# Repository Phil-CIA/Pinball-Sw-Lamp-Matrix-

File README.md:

# Pinball Switch + Lamp Matrix Board

8x4 lamp matrix driver and 8x4 switch matrix scanner board for a pinball machine.

## Architecture (current)
- **Lamp rows (8):** high-side smart switches (2× `VNQ7E100AJTR`, 4ch each)
- **Lamp columns (4):** low-side MOSFET sinks
- **Switch columns (4):** `LMV393` comparators (5V powered, OD outputs pulled up to 3.3V)
- **Output expansion:** 2× `74HC595` @ 3.3V for deterministic row/column bit patterns

## Repo layout
- `hardware/` – KiCad project files and production exports
- `firmware/` – PlatformIO / ESP-IDF bring-up firmware
- `docs/` – design notes, project status, review notes, and bring-up plans
- `BOM/` – key part numbers and alternates

## Project references
- `docs/PROJECT_STATUS.md` – current state, locked assumptions, and active priorities
- `docs/NEXT_ITERATION.md` – parking lot for ideas, risks, and restart notes
- `docs/SCHEMATIC_REVIEW.md` – design review and cleanup notes captured during the pre-order review
- `docs/BRINGUP_CHECKLIST.md` – first-board arrival, assembly, and power-up checklist
- `docs/PINMAP.md` – signal naming, connector grouping, and board-mating draft map
- `docs/PCB_REVIEW_CHECKLIST.md` – pre-order hardware checklist
- `docs/GITHUB_REPO_SETUP.md` – suggested GitHub repo metadata and settings
- `BOM/key_parts.md` – important component choices
- `CONTRIBUTING.md` – repo workflow and update expectations
- `SECURITY.md` – reporting guidance for risky or security-related issues
- `CHANGELOG.md` – notable repo changes over time

## Status
Rev 1 hardware was ordered on **2026-04-09**.

- **Hardware:** schematic, PCB snapshots, Gerbers, drill files, BOM, and production ZIP are checked in under `hardware/`
- **Order state:** PCB + stencil ordered, with parts ordered separately
- **Current phase:** wait for hardware and prepare bench bring-up
- **Firmware:** verified ESP32-C6 ESP-IDF bring-up scaffold is present under `firmware/`

## Next Steps
- keep the ordered Rev 1 package and notes as the reference point
- assemble and inspect the first boards when they arrive
- short-check `18V`, `5V`, and `3.3V` before full power-up
- validate ESP32, shift-register outputs, and switch-column reads on bench hardware
- run one-row / one-column lamp tests, then a full matrix scan
- capture any Rev 2 findings after first hardware validation

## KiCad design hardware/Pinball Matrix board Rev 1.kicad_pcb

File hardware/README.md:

# Hardware Notes

This folder contains the KiCad project files and production exports for the pinball switch + lamp matrix board.

## Current state
- `Pinball Matrix board Rev 1.kicad_sch` is the checked-in schematic source for Rev 1.
- `hardware/` also contains routed PCB snapshots, Gerbers, drill files, a BOM CSV, and the zipped production package used for ordering.
- Rev 1 PCB + stencil were ordered on `2026-04-09`; treat the ordered files as the frozen reference until hardware bring-up starts.

## Recommended use
1. Use `../docs/SCHEMATIC_REVIEW.md` for design review context and accepted tradeoffs.
2. Use `../docs/BRINGUP_CHECKLIST.md` when the first boards arrive.
3. Record any assembly or bench findings back into `../docs/NEXT_ITERATION.md` and `../docs/PROJECT_STATUS.md`.

## Caution
- More than one PCB snapshot exists in this folder (`pre route`, `routed`, `routed power`).
- If a post-order edit is made, clearly note whether it belongs to the frozen Rev 1 archive or to future Rev 2 work.

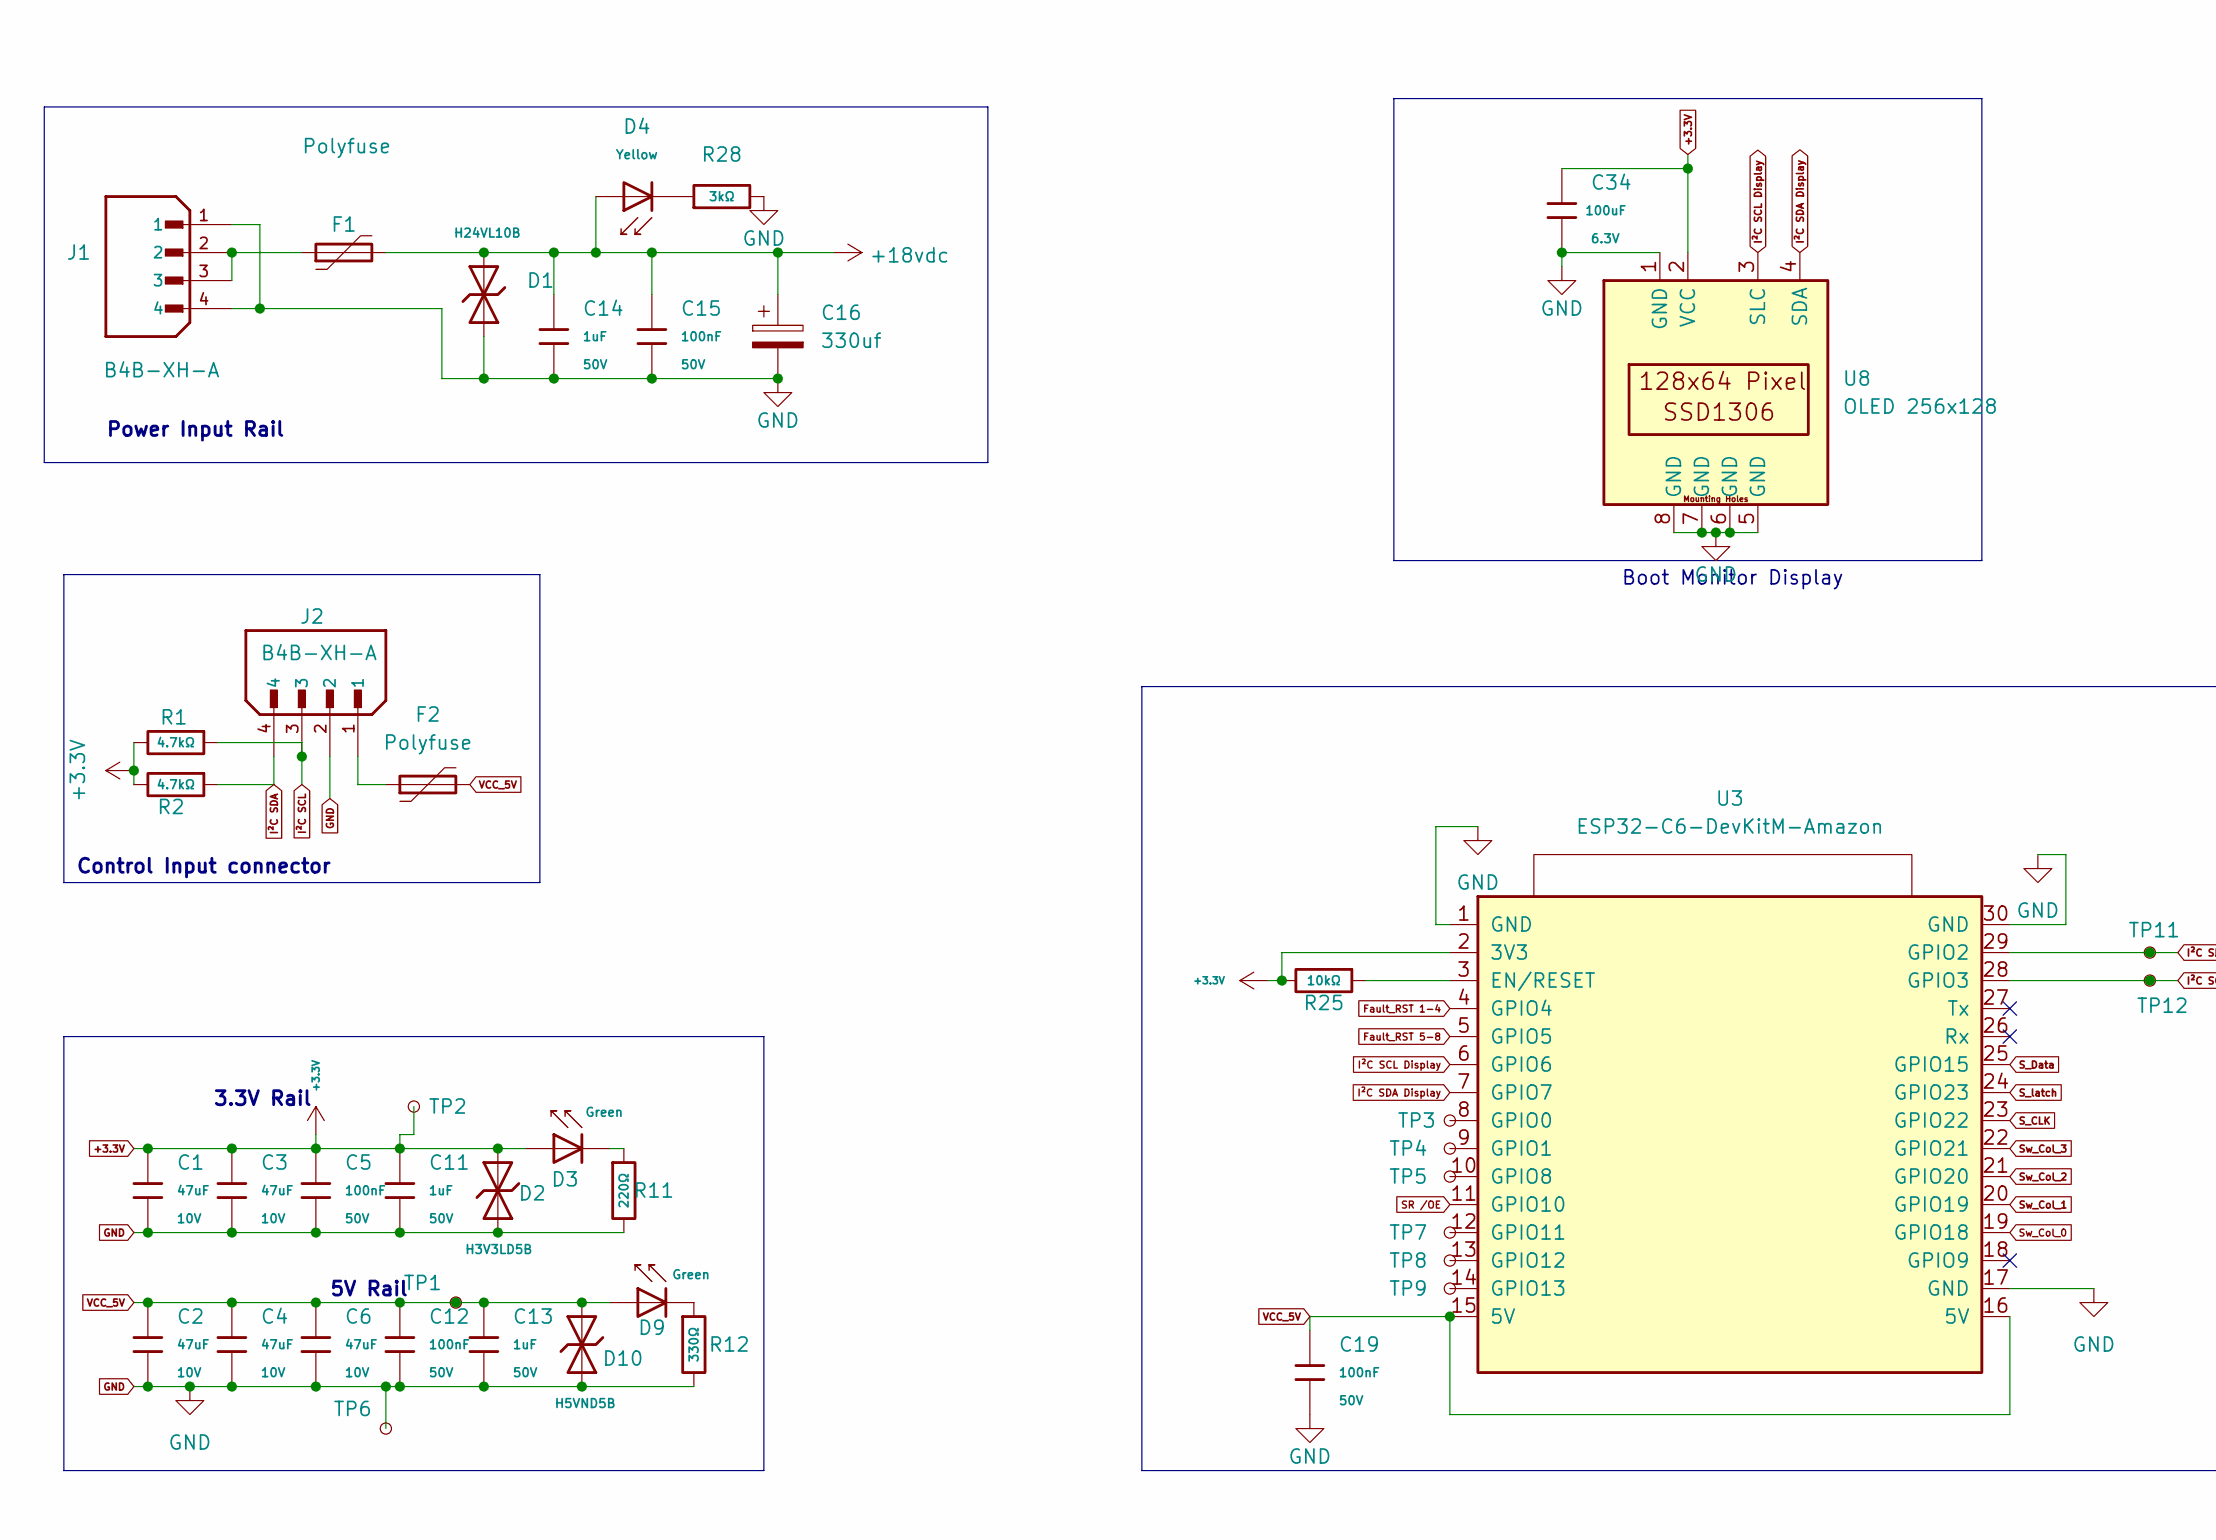
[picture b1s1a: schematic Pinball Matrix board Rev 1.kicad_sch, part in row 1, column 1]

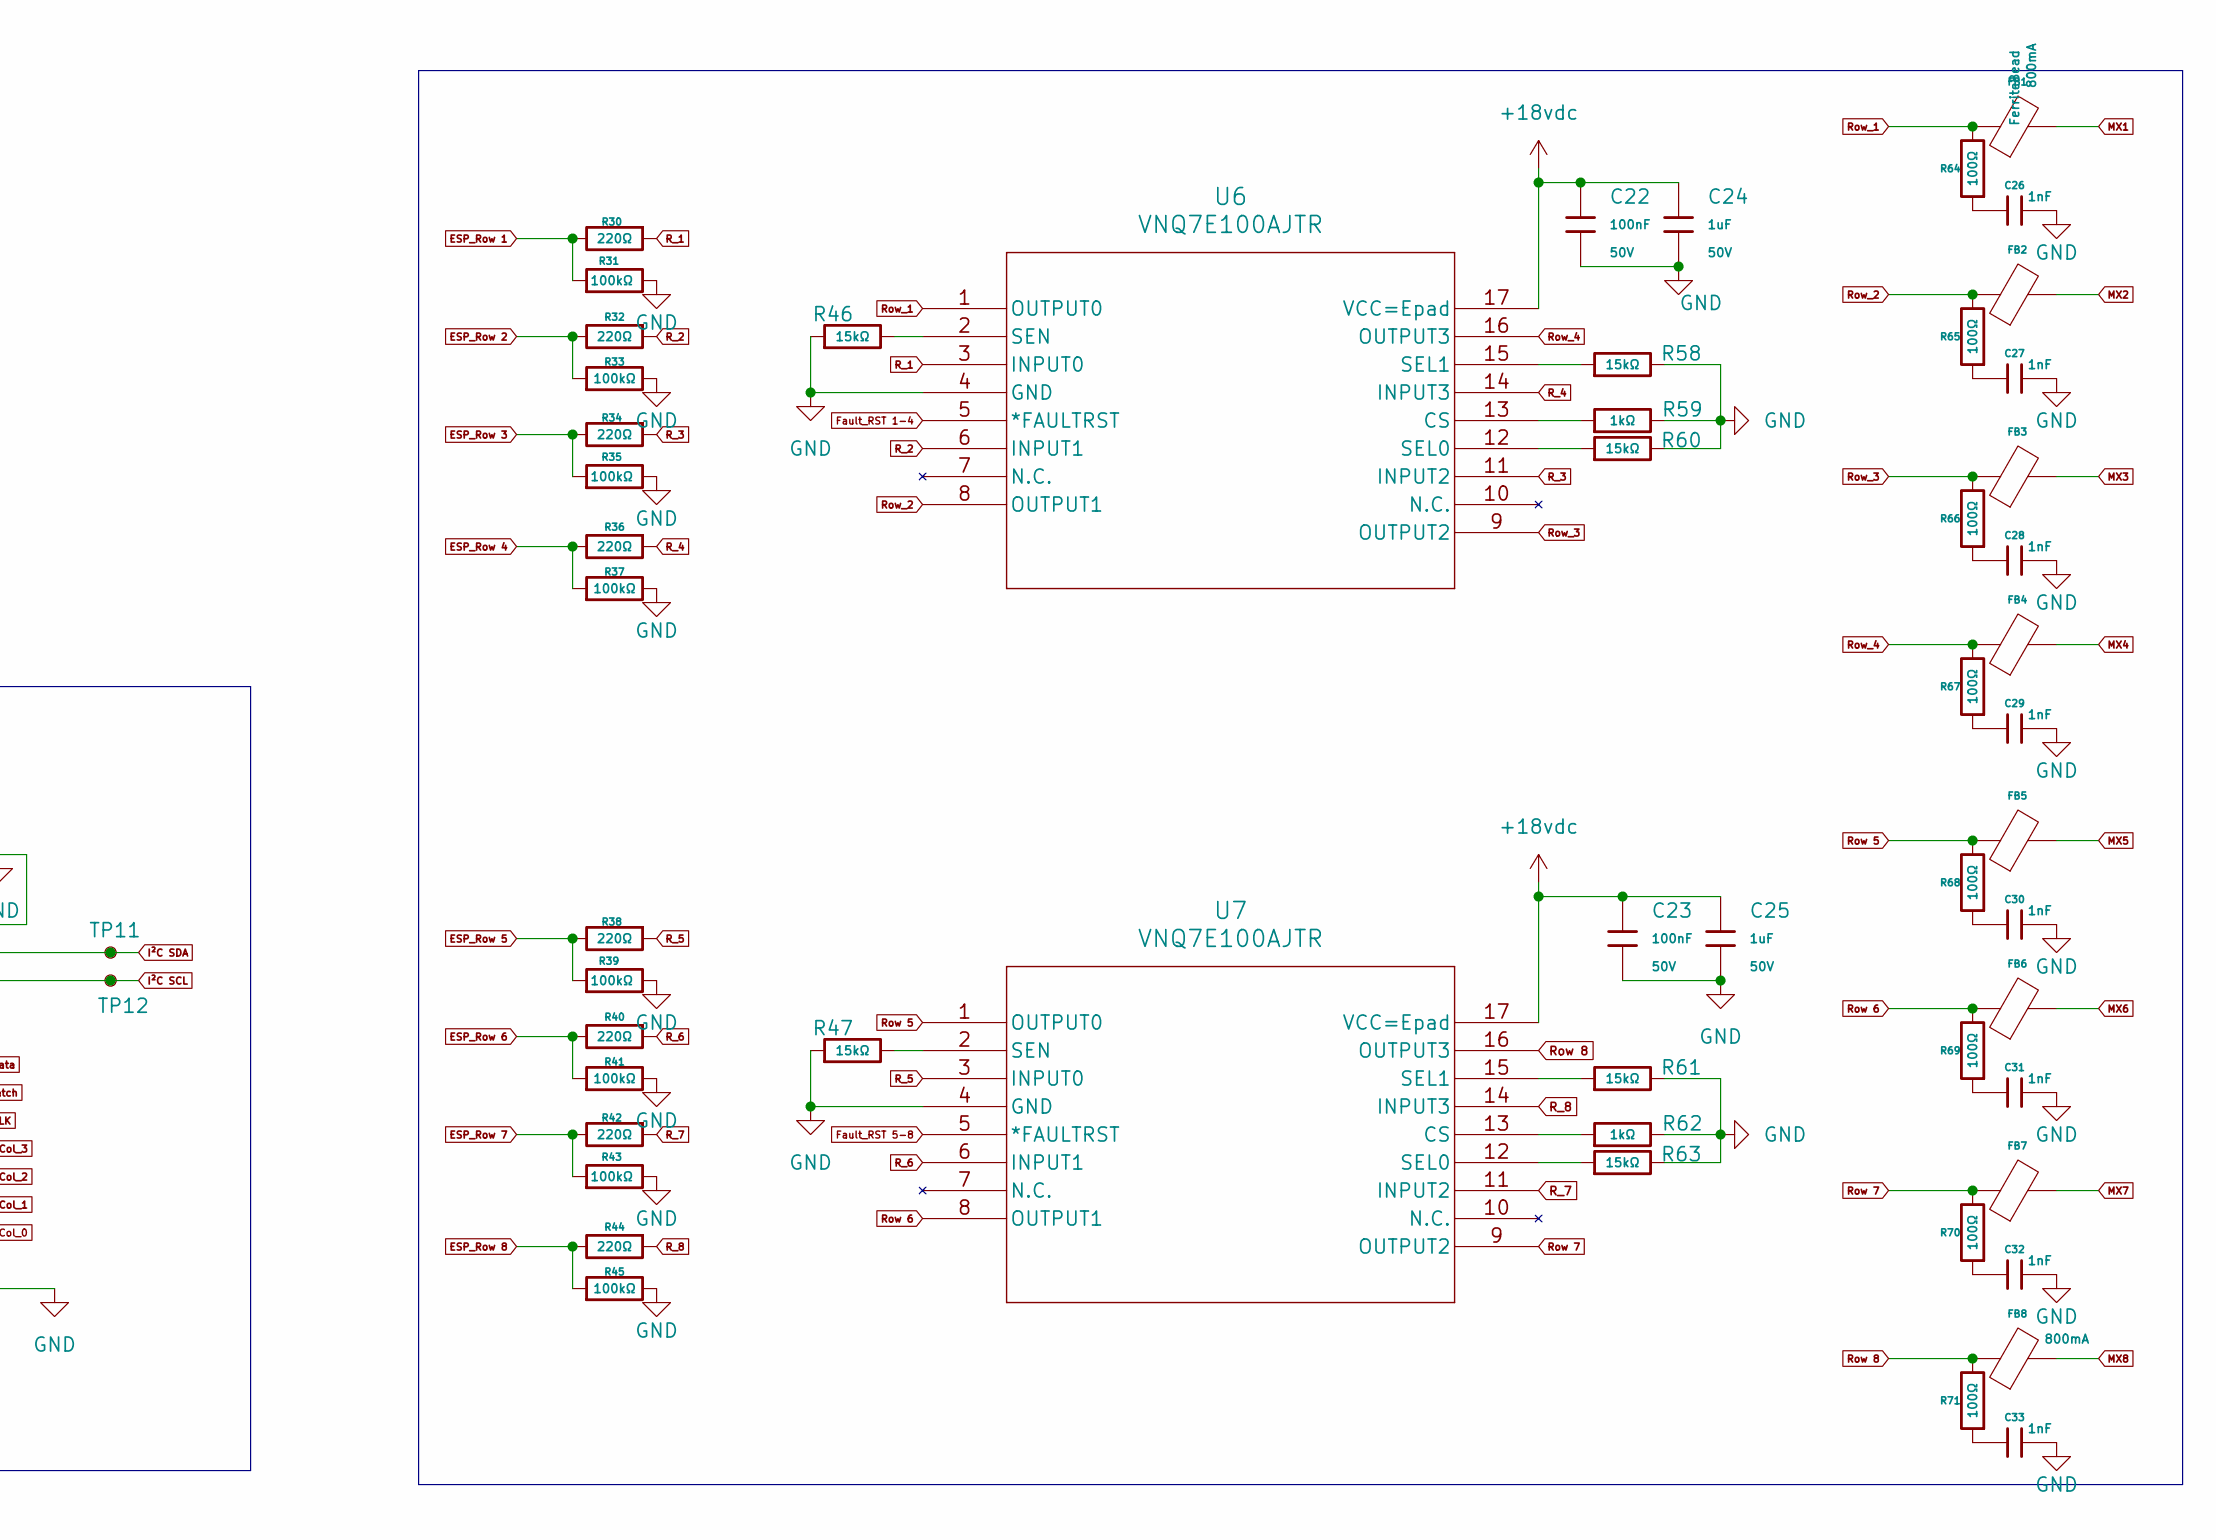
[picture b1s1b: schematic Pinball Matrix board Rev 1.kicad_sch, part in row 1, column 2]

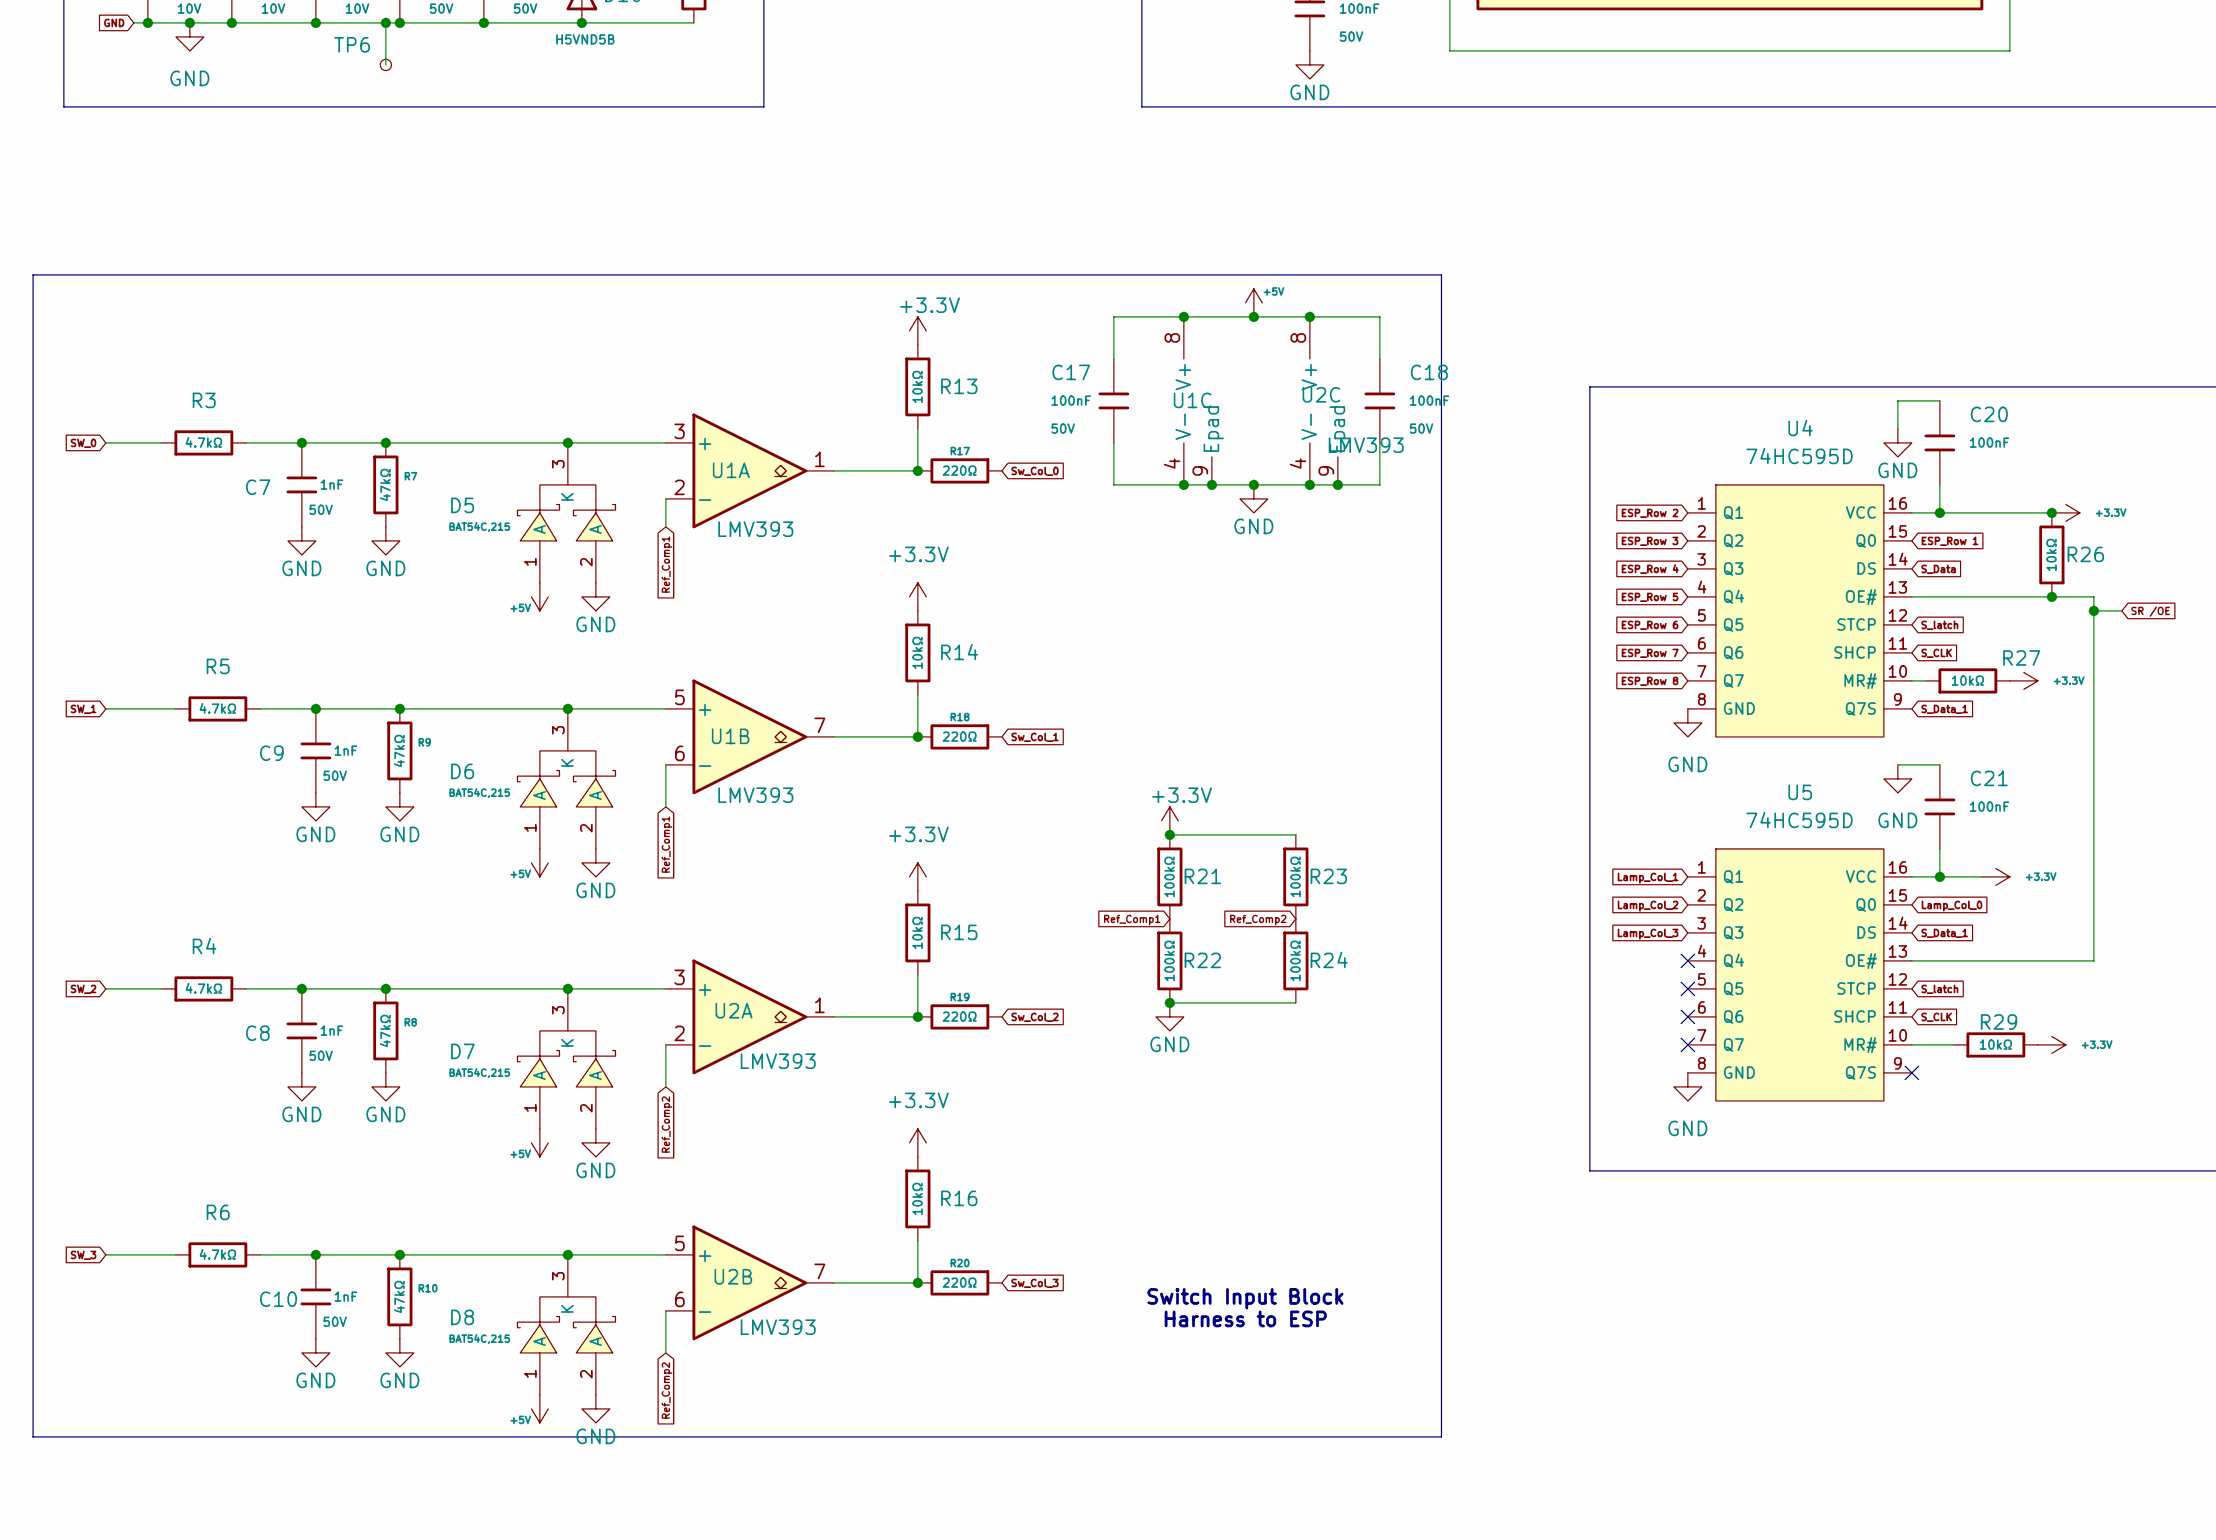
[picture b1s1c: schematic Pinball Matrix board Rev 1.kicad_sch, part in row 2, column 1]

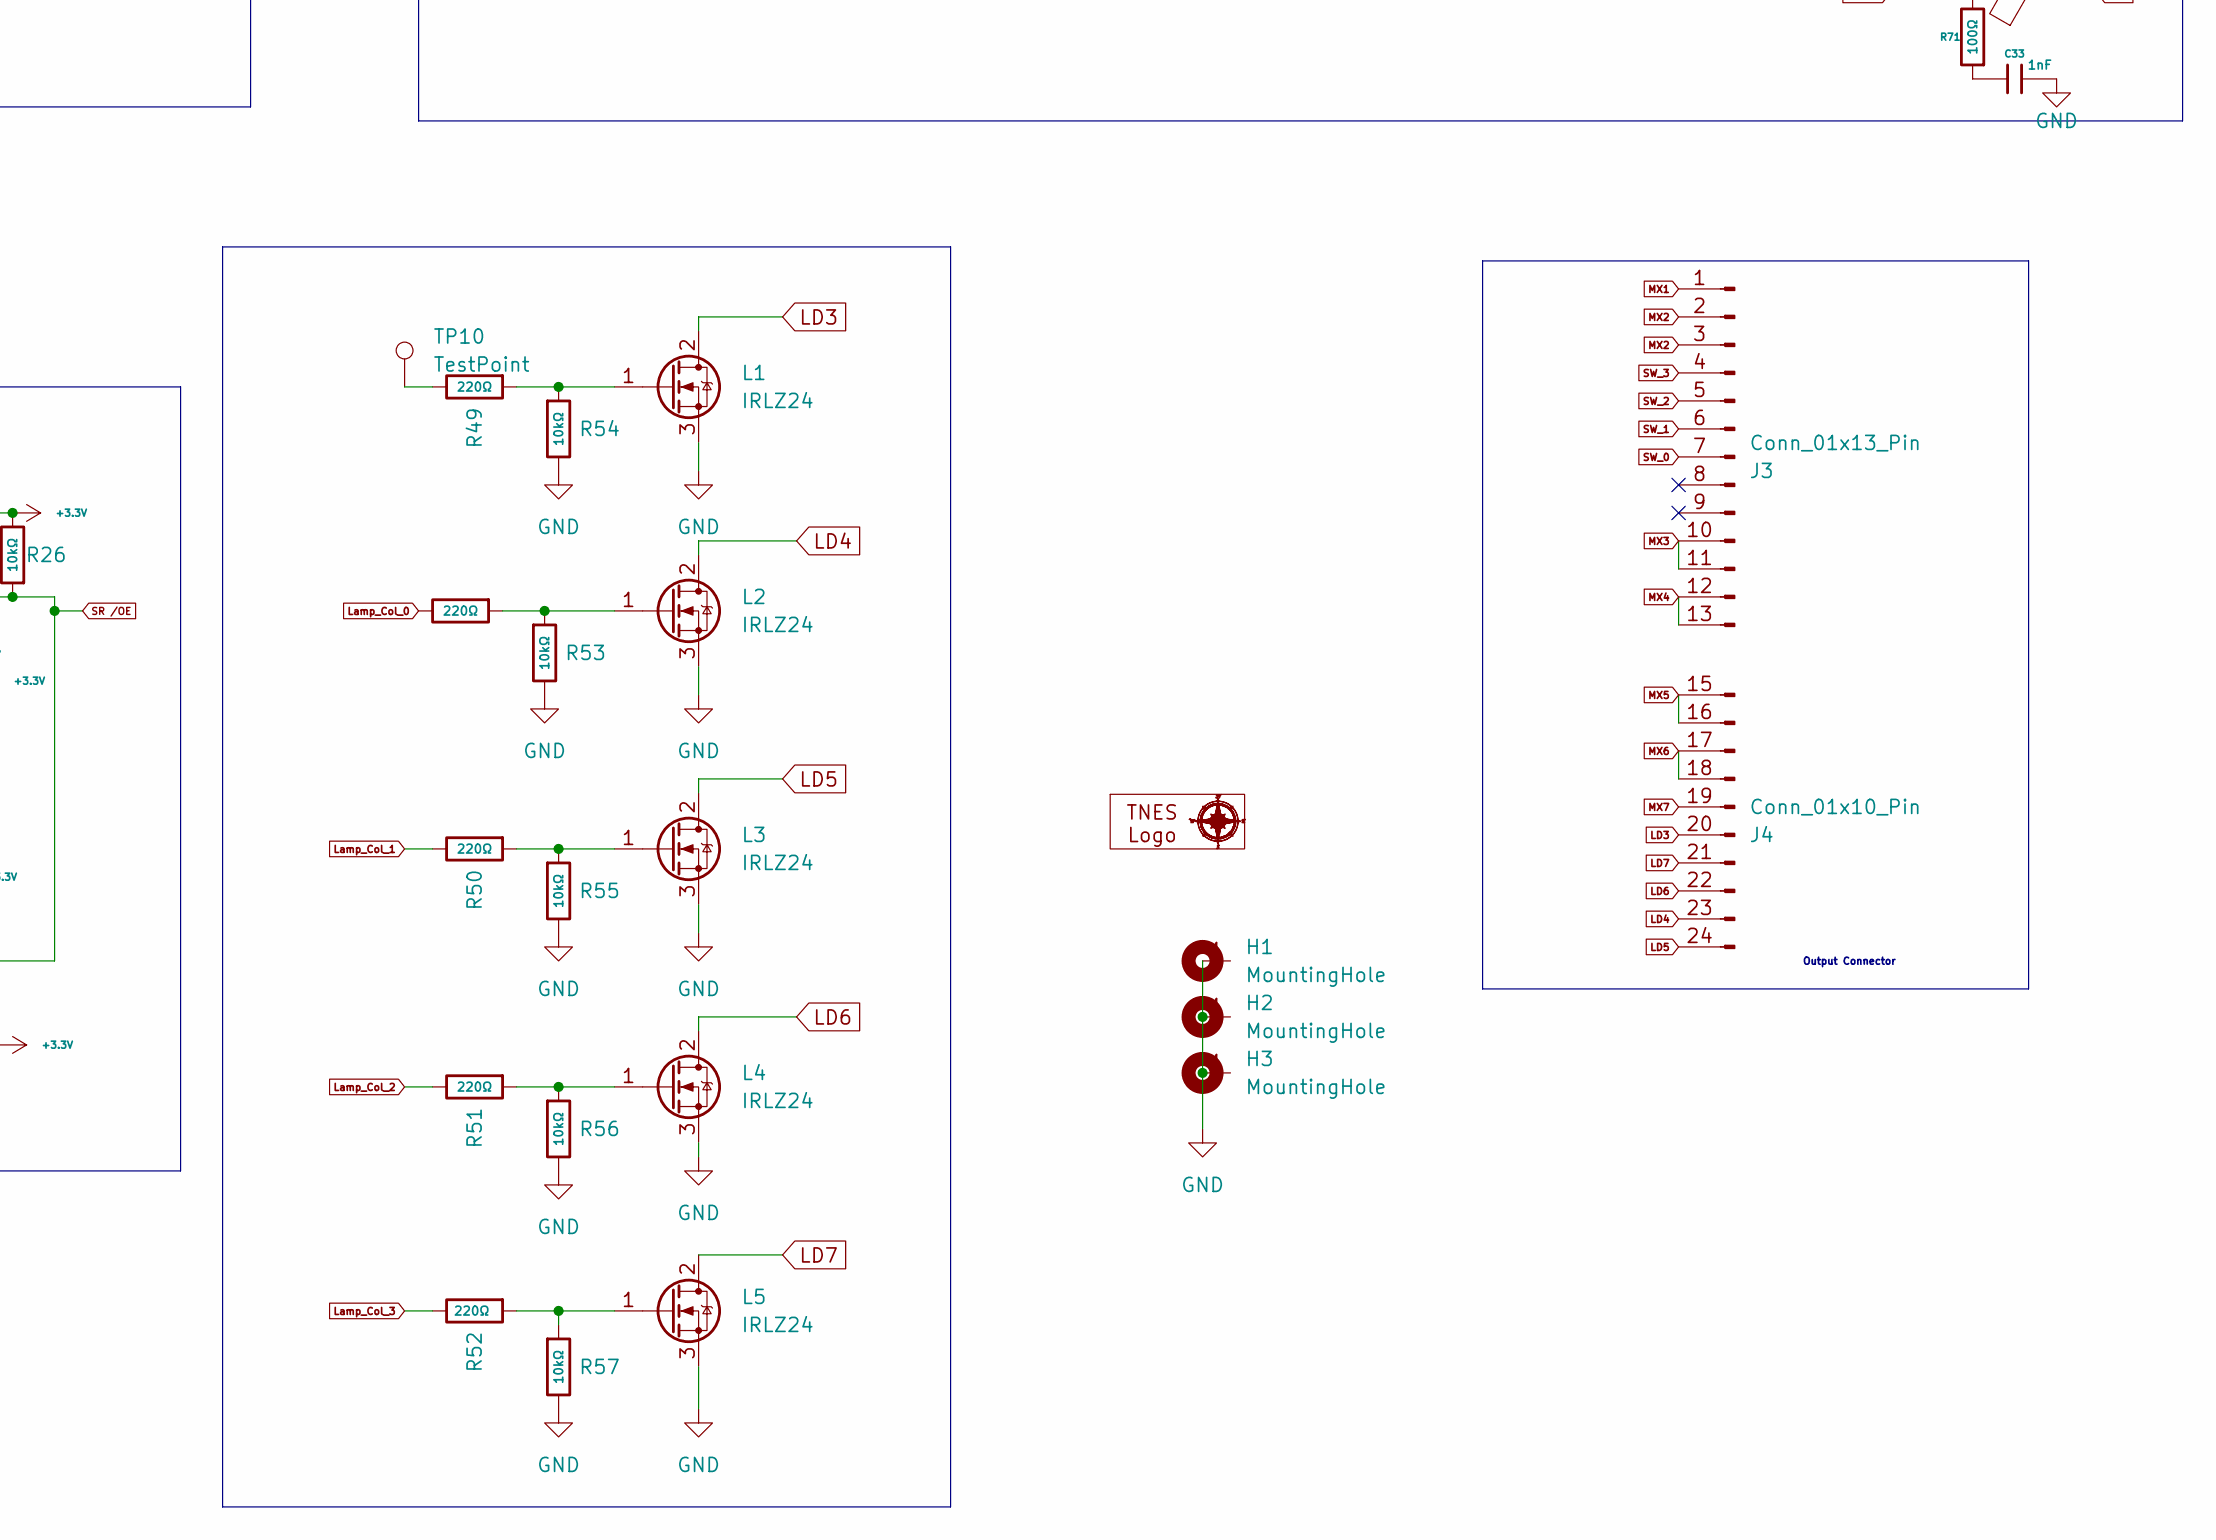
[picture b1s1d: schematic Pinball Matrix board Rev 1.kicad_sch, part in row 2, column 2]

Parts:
10mm1: 10mm LOGO
C1, C2, C3, C4, C6: 47uF; C_1206; Voltage Rated 10V; Tolerance ±20%; Part CL31A476MPHNNNE; LCSC C96123
C5, C12, C15, C17, C18, C19, C20, C21, C22, C23: 100nF; C_0805; Voltage Rated 50V; Tolerance ±10%; Part CC0805KRX7R9BB104; LCSC C49678
C7, C8, C9, C10, C26, C27, C28, C29, C30, C31, C32, C33: 1nF; C_0805; Voltage Rated 50V; Tolerance ±10%; Part CL21B102KBCNNNC; LCSC C46653
C11, C13, C14, C24, C25: 1uF; C_0805; Voltage Rated 50V; Tolerance ±10%; Part CL21B105KBFNNNE; LCSC C28323
C16: 330uf; CP_Radial_D6.3mm_P2.50mm; LCSC C122240
C34: 100uF; C_1206; Voltage Rated 6.3V; Tolerance ±20%; Part CL31A107MQHNNNE; LCSC C15008
D1: H24VL10B; D_DFN1006-2L; Part H24VL10B; LCSC C20617912
D2: H3V3LD5B; D_SOD-523; Breakdown Voltage 5.5V; Part H3V3LD5B; LCSC C20615817
D3, D9: Green; D_0805; Part KT-0805G; LCSC C2297
D4: Yellow; D_0805; Part KT-0805Y; LCSC C2296
D5, D6, D7, D8: BAT54C,215; SOT-23-3_L2.9-W1.6-P1.90-LS2.8-BR; Reverse Voltage (Vr) 30V; Forward Voltage (Vf@If) 800mV@100mA; Part BAT54C,215; LCSC C37704
D10: H5VND5B; D_SOD-523; Part H5VND5B; LCSC C20615818
F1: Polyfuse; poly fuse; LCSC C49166597
F2: Polyfuse; L_1206; LCSC C720075
FB1, FB2, FB3, FB4, FB5, FB6, FB7: FerriteBead; L_1206; Current Rating 800mA; Tolerance ±25%; Part GZ2012D101TF; LCSC C1015
FB8: FerriteBead; FB_0805; Current Rating 800mA; Tolerance ±25%; Part GZ2012D101TF; LCSC C1015
H1, H2, H3: MountingHole; MountingHole_3.5mm_Pad
J1, J2: B4B-XH-A; JST_EH_B4B-EH-A_1x04_P2.50mm_Vertical; PARTREV 7/4/21
J3: Conn_01x13_Pin; Molex_KK-396_A-41791-0013_1x13_P3.96mm_Vertical
J4: Conn_01x10_Pin; Molex_KK-396_A-41791-0010_1x10_P3.96mm_Vertical
L1: IRLZ24; TO-252-2; Manufacturer_Part_Number IRLZ44NPBF; LCSC C3007
L2, L3, L4, L5: IRLZ24; TO-252-2; Mouser Part Number 942-IRLZ44NPBF
R1, R2, R3, R4, R5, R6: 4.7kΩ; R_0805; Overload Voltage (Max) 150V; Tolerance ±1%; Part 0805W8F4701T5E; LCSC C17673
R7, R8, R9, R10: 47kΩ; R_0805; Overload Voltage (Max) 150V; Tolerance ±1%; Part 0805W8F4702T5E; LCSC C17713
R11, R17, R18, R19, R20, R30, R32, R34, R36, R38, R40, R42, R44, R48, R49, R50, R51, R52: 220Ω; R_0805; Overload Voltage (Max) 150V; Tolerance ±1%; Part 0805W8F2200T5E; LCSC C17557
R12: 330Ω; R_0805; Overload Voltage (Max) 150V; Tolerance ±1%; Part 0805W8F3300T5E; LCSC C17630
R13, R14, R15, R16, R25, R26, R27, R29, R53, R54, R55, R56, R57: 10kΩ; R_0805; Overload Voltage (Max) 150V; Tolerance ±1%; Part 0805W8F1002T5E; LCSC C17414
R21, R22, R23, R24, R31, R33, R35, R37, R39, R41, R43, R45: 100kΩ; R_0805; Overload Voltage (Max) 150V; Tolerance ±1%; Part 0805W8F1003T5E; LCSC C149504
R28: 3kΩ; R_0805; Overload Voltage (Max) 150V; Tolerance ±1%; Part 0805W8F3001T5E; LCSC C17661
R46, R47, R58, R60, R61, R63: 15kΩ; R_0805; Overload Voltage (Max) 150V; Tolerance ±1%; Part 0805W8F1502T5E; LCSC C17475
R59, R62: 1kΩ; R_0805; Overload Voltage (Max) 150V; Tolerance ±1%; Part 0805W8F1001T5E; LCSC C17513
R64, R65, R66, R67, R68, R69, R70, R71: 100Ω; R_0805; Overload Voltage (Max) 150V; Tolerance ±1%; Part 0805W8F1000T5E; LCSC C17408
TP1, TP2, TP3, TP4, TP5, TP6, TP7, TP8, TP9, TP11, TP12: TestPoint_Small; KEYSTONE_5015
TP10: TestPoint; PinSocket_1x01_P2.54mm_Vertical
U1, U2: LMV393; SOIC-8-1EP_3.9x4.9mm_P1.27mm_EP2.29x3mm; LCSC C7984
U3: ESP32-C6-DevKitM-Amazon; ESP32-C6-DevKit-Amazon
U4, U5: 74HC595D; SOIC-16_L9.9-W3.9-P1.27-LS6.0-BL; Supply Voltage 2V~6V; Part 74HC595D,118; LCSC C5947
U6, U7: VNQ7E100AJTR; SOP50P600X148-17N; LCSC C2969931
U8: OLED 256x128; 0.96 inOLED display SSD1306

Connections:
+3.3V: C1.1, C3.1, C5.1, C11.1, C20.2, C21.2, C34.1, D2.2, D3.2, R1.2, R2.2, R13.1, R14.1, R15.1, R16.1, R21.1, R23.1, R25.2, R26.2, R27.2, R29.2, TP2.1, U3.2 (3V3), U4.16 (VCC), U5.16 (VCC), U8.2 (VCC)
+5V: C17.1, C18.1, D5.1 (A), D6.1 (A), D7.1 (A), D8.1 (A), U1.8 (V+), U2.8 (V+)
+18vdc: C14.1, C15.1, C16.1, C22.1, C23.1, C24.1, C25.1, D1.2, D4.2, F1.2, U6.17 (VCC=Epad), U7.17 (VCC=Epad)
ESP_Row 1: R30.2, R31.1, U4.15 (Q0)
ESP_Row 2: R32.2, R33.1, U4.1 (Q1)
ESP_Row 3: R34.2, R35.1, U4.2 (Q2)
ESP_Row 4: R36.2, R37.1, U4.3 (Q3)
ESP_Row 5: R38.2, R39.1, U4.4 (Q4)
ESP_Row 6: R40.2, R41.1, U4.5 (Q5)
ESP_Row 7: R42.2, R43.1, U4.6 (Q6)
ESP_Row 8: R44.2, R45.1, U4.7 (Q7)
Fault_RST 1-4: U3.4 (GPIO4), U6.5 (*FAULTRST)
Fault_RST 5-8: U3.5 (GPIO5), U7.5 (*FAULTRST)
GND: C1.2, C2.2, C3.2, C4.2, C5.2, C6.2, C7.2, C8.2, C9.2, C10.2, C11.2, C12.2, C13.2, C14.2, C15.2, C16.2, C17.2, C18.2, C19.2, C20.1, C21.1, C22.2, C23.2, C24.2, C25.2, C26.2, C27.2, C28.2, C29.2, C30.2, C31.2, C32.2, C33.2, C34.2, D1.1, D2.1, D5.2 (A), D6.2 (A), D7.2 (A), D8.2 (A), D10.1, H1.1, H2.1, H3.1, J1.1, J1.4, J2.2, L1.3 (S), L2.3 (S), L3.3 (S), L4.3 (S), L5.3 (S), R7.2, R8.2, R9.2, R10.2, R11.2, R12.2, R22.2, R24.2, R28.2, R31.2, R33.2, R35.2, R37.2, R39.2, R41.2, R43.2, R45.2, R46.1, R47.1, R53.2, R54.2, R55.2, R56.2, R57.2, R58.2, R59.2, R60.2, R61.2, R62.2, R63.2, TP6.1, U1.4 (V-), U1.9 (Epad), U2.4 (V-), U2.9 (Epad), U3.1 (GND), U3.17 (GND), U3.30 (GND), U4.8 (GND), U5.8 (GND), U6.4 (GND), U7.4 (GND), U8.1 (GND), U8.5 (GND), U8.6 (GND), U8.7 (GND), U8.8 (GND)
I²C SCL: J2.3, R1.1, TP12.1, U3.28 (GPIO3)
I²C SCL Display: U3.6 (GPIO6), U8.3 (SLC)
I²C SDA: J2.4, R2.1, TP11.1, U3.29 (GPIO2)
I²C SDA Display: U3.7 (GPIO7), U8.4 (SDA)
LD3: J4.20 (Pin_6), L1.2 (D)
LD4: J4.23 (Pin_9), L2.2 (D)
LD5: J4.24 (Pin_10), L3.2 (D)
LD6: J4.22 (Pin_8), L4.2 (D)
LD7: J4.21 (Pin_7), L5.2 (D)
Lamp_Col_0: R48.2, U5.15 (Q0)
Lamp_Col_1: R50.2, U5.1 (Q1)
Lamp_Col_2: R51.2, U5.2 (Q2)
Lamp_Col_3: R52.2, U5.3 (Q3)
MX1: FB1.2, J3.1
MX2: FB2.2, J3.2, J3.3
MX3: FB3.2, J3.10, J3.11
MX4: FB4.2, J3.12, J3.13
MX5: FB5.2, J4.15 (Pin_1), J4.16 (Pin_2)
MX6: FB6.2, J4.17 (Pin_3), J4.18 (Pin_4)
MX7: FB7.2, J4.19 (Pin_5)
unnamed: C26.1, R64.1
unnamed: C27.1, R65.1
unnamed: C28.1, R66.1
unnamed: C29.1, R67.1
unnamed: C30.1, R68.1
unnamed: C31.1, R69.1
unnamed: C32.1, R70.1
unnamed: C33.1, R71.1
unnamed: D3.1, R11.1
unnamed: D4.1, R28.1
unnamed: C7.1, D5.3 (K), R3.2, R7.1, U1.3 (+)
unnamed: C9.1, D6.3 (K), R5.2, R9.1, U1.5 (+)
unnamed: C8.1, D7.3 (K), R4.2, R8.1, U2.3 (+)
unnamed: C10.1, D8.3 (K), R6.2, R10.1, U2.5 (+)
unnamed: D9.1, R12.1
unnamed: F1.1, J1.2, J1.3
unnamed: F2.1, J2.1
unnamed: L1.1 (G), R49.1, R54.1
unnamed: L2.1 (G), R48.1, R53.1
unnamed: L3.1 (G), R50.1, R55.1
unnamed: L4.1 (G), R51.1, R56.1
unnamed: L5.1 (G), R52.1, R57.1
unnamed: R13.2, R17.2, U1.1
unnamed: R14.2, R18.2, U1.7
unnamed: R15.2, R19.2, U2.1
unnamed: R16.2, R20.2, U2.7
unnamed: R49.2, TP10.1
unnamed: R25.1, U3.3 (EN/RESET)
unnamed: TP3.1, U3.8 (GPIO0)
unnamed: TP4.1, U3.9 (GPIO1)
unnamed: TP5.1, U3.10 (GPIO8)
unnamed: TP7.1, U3.12 (GPIO11)
unnamed: TP8.1, U3.13 (GPIO12)
unnamed: TP9.1, U3.14 (GPIO13)
unnamed: R27.1, U4.10 (MR#)
unnamed: R29.1, U5.10 (MR#)
unnamed: R59.1, U6.13 (CS)
unnamed: R60.1, U6.12 (SEL0)
unnamed: R58.1, U6.15 (SEL1)
unnamed: R46.2, U6.2 (SEN)
unnamed: R62.1, U7.13 (CS)
unnamed: R63.1, U7.12 (SEL0)
unnamed: R61.1, U7.15 (SEL1)
unnamed: R47.2, U7.2 (SEN)
R_1: R30.1, U6.3 (INPUT0)
R_2: R32.1, U6.6 (INPUT1)
R_3: R34.1, U6.11 (INPUT2)
R_4: R36.1, U6.14 (INPUT3)
R_5: R38.1, U7.3 (INPUT0)
R_6: R40.1, U7.6 (INPUT1)
R_7: R42.1, U7.11 (INPUT2)
R_8: R44.1, U7.14 (INPUT3)
Ref_Comp1: R21.2, R22.1, U1.2 (-), U1.6 (-)
Ref_Comp2: R23.2, R24.1, U2.2 (-), U2.6 (-)
Row 5: FB5.1, R68.2, U7.1 (OUTPUT0)
Row 6: FB6.1, R69.2, U7.8 (OUTPUT1)
Row 7: FB7.1, R70.2, U7.9 (OUTPUT2)
Row 8: FB8.1, R71.2, U7.16 (OUTPUT3)
Row_1: FB1.1, R64.2, U6.1 (OUTPUT0)
Row_2: FB2.1, R65.2, U6.8 (OUTPUT1)
Row_3: FB3.1, R66.2, U6.9 (OUTPUT2)
Row_4: FB4.1, R67.2, U6.16 (OUTPUT3)
SR /OE: R26.1, U3.11 (GPIO10), U4.13 (OE#), U5.13 (OE#)
SW_0: J3.7, R3.1
SW_1: J3.6, R5.1
SW_2: J3.5, R4.1
SW_3: J3.4, R6.1
S_CLK: U3.23 (GPIO22), U4.11 (SHCP), U5.11 (SHCP)
S_Data: U3.25 (GPIO15), U4.14 (DS)
S_Data_1: U4.9 (Q7S), U5.14 (DS)
S_latch: U3.24 (GPIO23), U4.12 (STCP), U5.12 (STCP)
Sw_Col_0: R17.1, U3.19 (GPIO18)
Sw_Col_1: R18.1, U3.20 (GPIO19)
Sw_Col_2: R19.1, U3.21 (GPIO20)
Sw_Col_3: R20.1, U3.22 (GPIO21)
VCC_5V: C2.1, C4.1, C6.1, C12.1, C13.1, C19.1, D9.2, D10.2, F2.2, TP1.1, U3.15 (5V), U3.16 (5V)

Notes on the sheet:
Boot Monitor Display
5V Rail
Switch Input Block Harness to ESP
Output Connector
3.3V Rail
Power Input Rail
Control Input connector

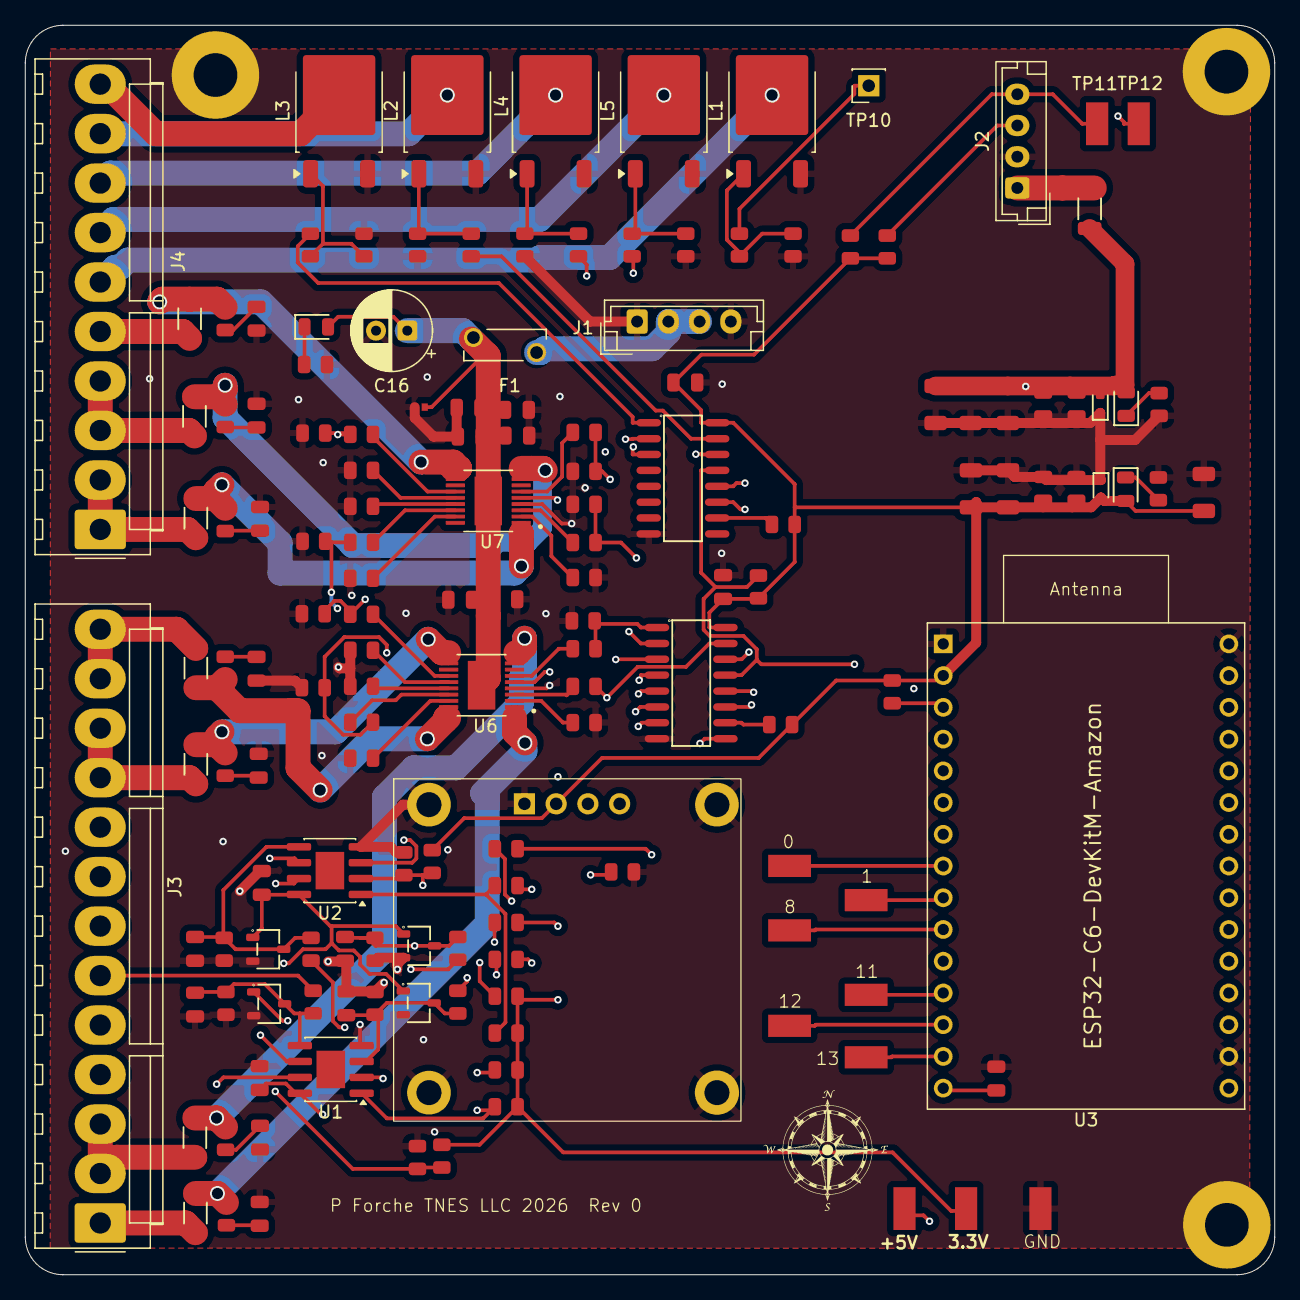
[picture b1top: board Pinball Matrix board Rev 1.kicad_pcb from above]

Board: 4 copper layers, 100.0 x 100.0 mm, 155 parts (0 on the bottom side), 108 nets.

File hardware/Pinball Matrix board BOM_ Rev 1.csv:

"Reference","Qty","Value","DNP","Exclude from BOM","Exclude from Board","LCSC","MANUFACTURER","Manufacturer_Part_Number","Part"
"10mm1","1","~","","Excluded from BOM","","","","",""
"C1,C2,C3,C4,C6","5","47uF","","","","C96123","","","CL31A476MPHNNNE"
"C5,C12,C15,C17,C18,C19,C20,C21,C22,C23","10","100nF","","","","C49678","","","CC0805KRX7R9BB104"
"C7,C8,C9,C10,C26,C27,C28,C29,C30,C31,C32,C33","12","1nF","","","","C46653","","","CL21B102KBCNNNC"
"C11,C13,C14,C24,C25","5","1uF","","","","C28323","","","CL21B105KBFNNNE"
"C16","1","330uf","","","","C122240","","",""
"C34","1","100uF","","","","C15008","","","CL31A107MQHNNNE"
"D1","1","H24VL10B","","","","C20617912","","","H24VL10B"
"D2","1","H3V3LD5B","","","","C20615817","","","H3V3LD5B"
"D3,D9","2","Green","","","","C2297","","","KT-0805G"
"D4","1","Yellow","","","","C2296","","","KT-0805Y"
"D5,D6,D7,D8","4","BAT54C,215","","","","C37704","","","BAT54C,215"
"D10","1","H5VND5B","","","","C20615818","","","H5VND5B"
"F1","1","Polyfuse","","","","C49166597","","",""
"F2","1","Polyfuse","","","","C720075","","",""
"FB1,FB2,FB3,FB4,FB5,FB6,FB7","7","FerriteBead","","","","C1015","","","GZ2012D101TF"
"FB8","1","FerriteBead","","","","C1015","","","GZ2012D101TF"
"H1,H2,H3","3","MountingHole","","Excluded from BOM","","","","",""
"J1,J2","2","B4B-XH-A","","","","","JST","",""
"J3","1","Conn_01x13_Pin","","","","","","",""
"J4","1","Conn_01x10_Pin","","","","","","",""
"L1,L2,L3,L4,L5","5","IRLZ24","","","","C3007","","IRLZ44NPBF",""
"R1,R2,R3,R4,R5,R6","6","4.7kΩ","","","","C17673","","","0805W8F4701T5E"
"R7,R8,R9,R10","4","47kΩ","","","","C17713","","","0805W8F4702T5E"
"R11,R17,R18,R19,R20,R30,R32,R34,R36,R38,R40,R42,R44,R48,R49,R50,R51,R52","18","220Ω","","","","C17557","","","0805W8F2200T5E"
"R12","1","330Ω","","","","C17630","","","0805W8F3300T5E"
"R13,R14,R15,R16,R25,R26,R27,R29,R53,R54,R55,R56,R57","13","10kΩ","","","","C17414","","","0805W8F1002T5E"
"R21,R22,R23,R24,R31,R33,R35,R37,R39,R41,R43,R45","12","100kΩ","","","","C149504","","","0805W8F1003T5E"
"R28","1","3kΩ","","","","C17661","","","0805W8F3001T5E"
"R46,R47,R58,R60,R61,R63","6","15kΩ","","","","C17475","","","0805W8F1502T5E"
"R59,R62","2","1kΩ","","","","C17513","","","0805W8F1001T5E"
"R64,R65,R66,R67,R68,R69,R70,R71","8","100Ω","","","","C17408","","","0805W8F1000T5E"
"TP1,TP2,TP3,TP4,TP5,TP6,TP7,TP8,TP9,TP11,TP12","11","TestPoint_Small","","","","","","",""
"TP10","1","TestPoint","","","","","","",""
"U1,U2","2","LMV393","","","","C7984","","",""
"U3","1","ESP32-C6-DevKitM-Amazon","","Excluded from BOM","","","","",""
"U4,U5","2","74HC595D","","","","C5947","","","74HC595D,118"
"U6,U7","2","VNQ7E100AJTR","","","","C2969931","","",""
"U8","1","OLED 256x128","","Excluded from BOM","","","","",""
